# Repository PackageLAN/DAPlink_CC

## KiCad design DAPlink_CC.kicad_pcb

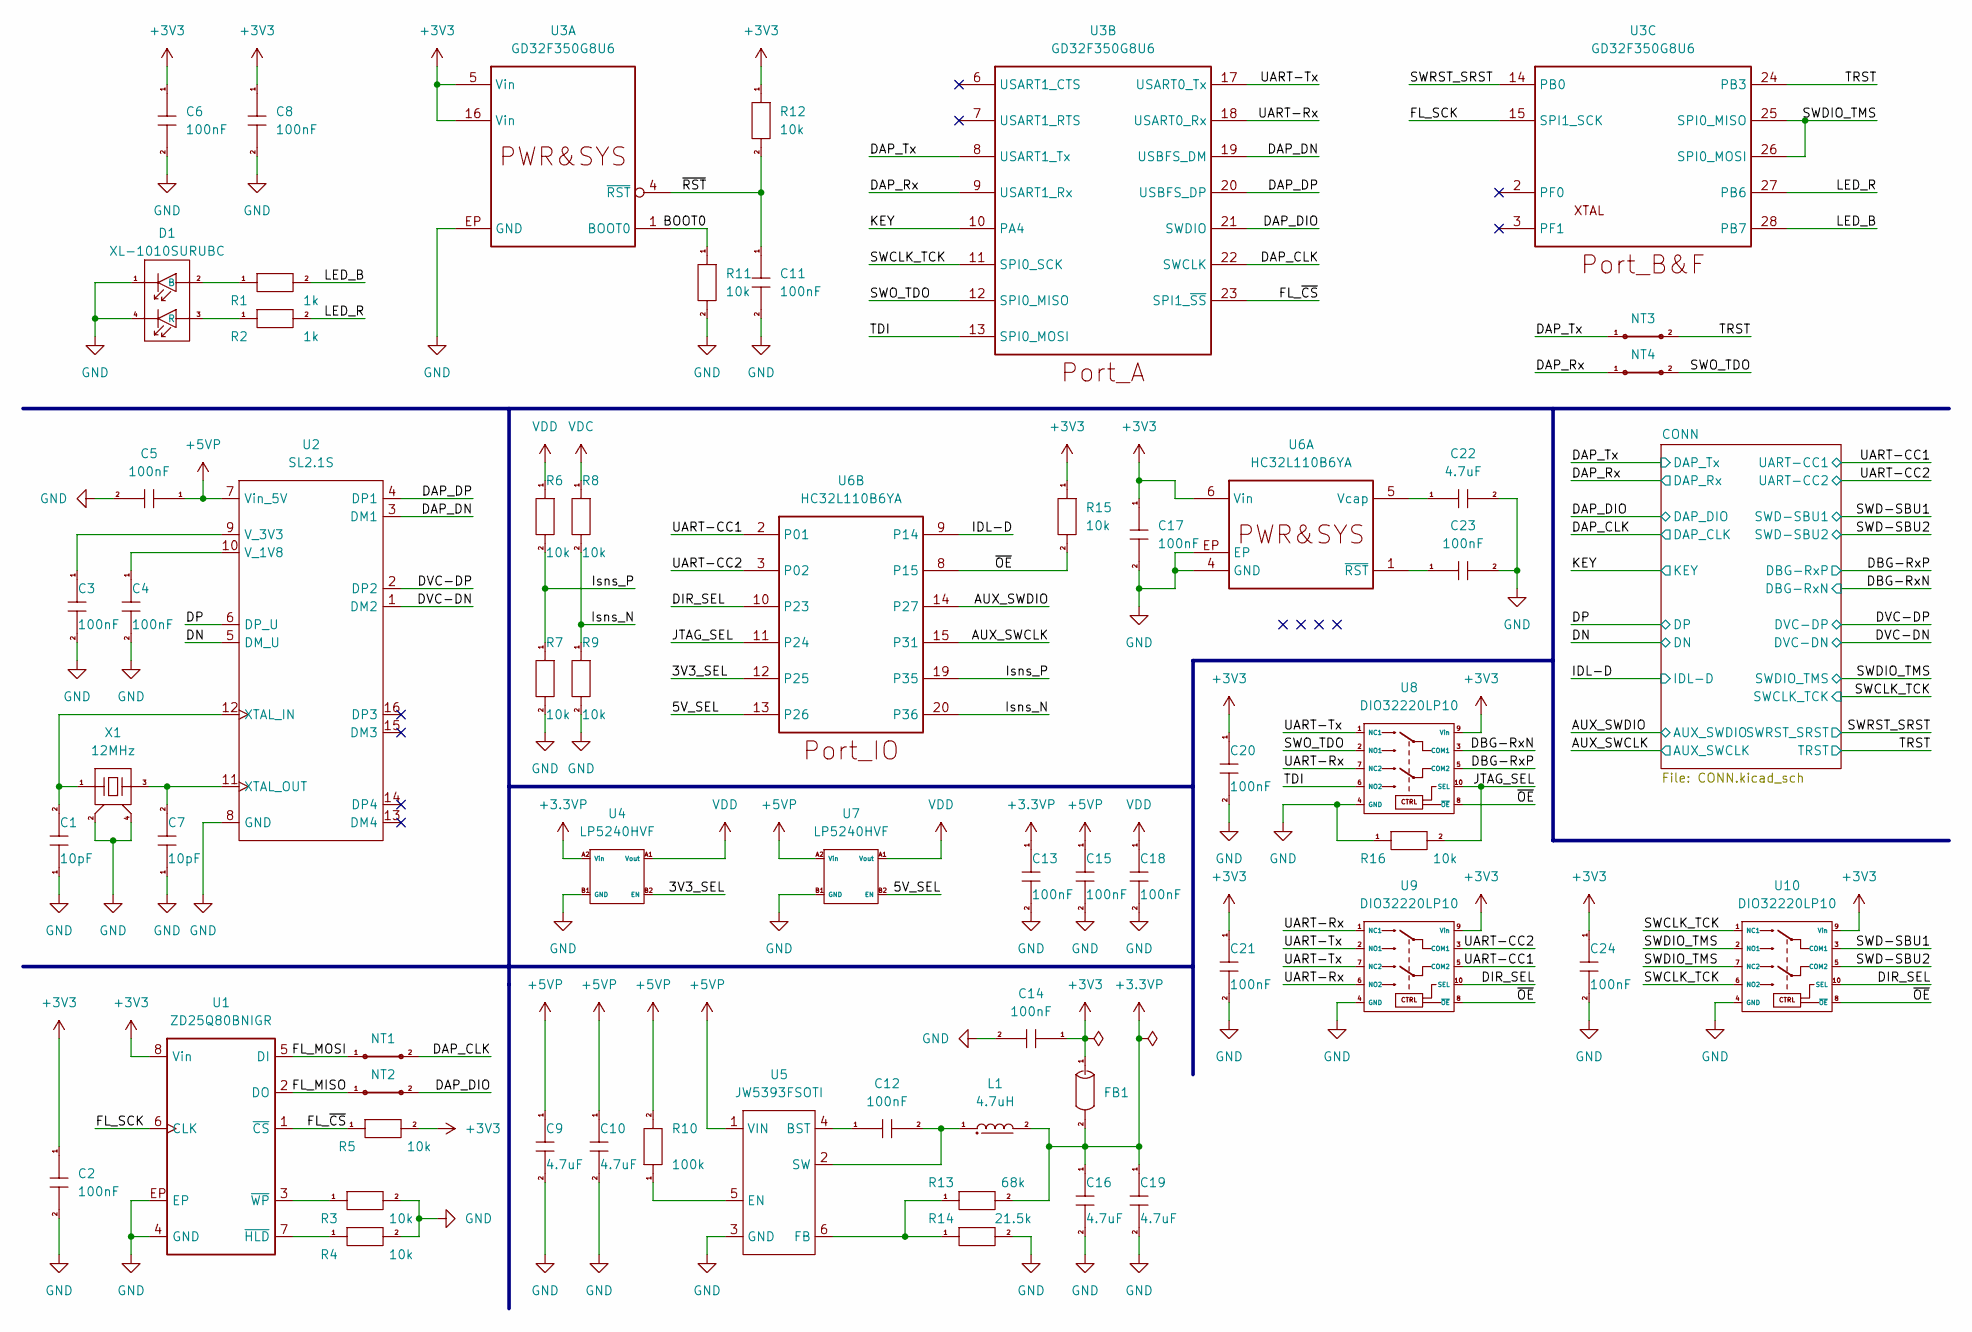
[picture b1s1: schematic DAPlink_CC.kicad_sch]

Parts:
C1, C7: 10pF; C0201(0603M)
C2, C3, C4, C5, C6, C8, C11, C12, C14, C17, C20, C21, C23, C24: 100nF; C0201(0603M)
C9, C10, C16, C19: 4.7uF; C0402(1005M)
C13, C15, C18: 100nF; C0402(1005M)
C22: 4.7uF; C0201(0603M)
D1: XL-1010SURUBC; LED-4_1010
FB1: 120R_100MHz; L0603(1608M)
L1: 4.7uH; MC-2520
NT1, NT2, NT3, NT4: NetCNVT-2; NetCNVT
R1, R2: 1k; R0201(0603M)
R3, R4, R5, R6, R7, R8, R9, R11, R12, R15, R16: 10k; R0201(0603M)
R10: 100k; R0201(0603M)
R13: 68k; R0201(0603M)
R14: 21.5k; R0201(0603M)
U1: ZD25Q80BNIGR; DFN-8_1515
U2: SL2.1S; MSOP-16_2646
U3: GD32F350G8U6; QFN-28_4040
U4, U7: LP5240HVF; CSP-4_S7575
U5: JW5393FSOTI; SOT-563
U6: HC32L110B6YA; QFN-20_3030
U8, U9, U10: DIO32220LP10; QFN-10_1814
X1: 12MHz; CXO-4_2520

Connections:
+3.3VP: C13.1, C16.1, C19.1, FB1.2, L1.2, R13.2, U4.A2 (Vin)
+3V3: C2.1, C6.1, C8.1, C14.1, C17.1, C20.1, C21.1, C24.1, FB1.1, R5.2, R12.1, R15.1, U1.8 (Vin), U3.5 (Vin), U3.16 (Vin), U6.6 (Vin), U8.9 (Vin), U9.9 (Vin), U10.9 (Vin); also elsewhere on the board
+5VP: C5.1, C9.1, C10.1, C15.1, R10.2, U2.7 (Vin_5V), U5.1 (VIN), U7.A2 (Vin); also elsewhere on the board
/3V3_SEL: U4.B2 (EN), U6.12 (P25)
/5V_SEL: U6.13 (P26), U7.B2 (EN)
/AUX_SWCLK: U6.15 (P31); also elsewhere on the board
/AUX_SWDIO: U6.14 (P27); also elsewhere on the board
/BOOT0: R11.1, U3.1 (BOOT0)
/DAP_CLK: NT1.2, U3.22 (SWCLK); also elsewhere on the board
/DAP_DIO: NT2.2, U3.21 (SWDIO); also elsewhere on the board
/DAP_DN: U2.3 (DM1), U3.19 (USBFS_DM)
/DAP_DP: U2.4 (DP1), U3.20 (USBFS_DP)
/DAP_Rx: NT4.1, U3.9 (USART1_Rx); also elsewhere on the board
/DAP_Tx: NT3.1, U3.8 (USART1_Tx); also elsewhere on the board
/DBG-RxN: U8.3 (COM1); also elsewhere on the board
/DBG-RxP: U8.5 (COM2); also elsewhere on the board
/DIR_SEL: U6.10 (P23), U9.10 (SEL), U10.10 (SEL)
/DN: U2.5 (DM_U); also elsewhere on the board
/DP: U2.6 (DP_U); also elsewhere on the board
/DVC-DN: U2.1 (DM2); also elsewhere on the board
/DVC-DP: U2.2 (DP2); also elsewhere on the board
/FL_MISO: NT2.1, U1.2 (DO)
/FL_MOSI: NT1.1, U1.5 (DI)
/FL_SCK: U1.6 (CLK), U3.15 (SPI1_SCK)
/FL_~CS: R5.1, U1.1 (~CS), U3.23 (SPI1_~SS)
/IDL-D: U6.9 (P14); also elsewhere on the board
/Isns_N: R8.2, R9.1, U6.20 (P36)
/Isns_P: R6.2, R7.1, U6.19 (P35)
/JTAG_SEL: R16.2, U6.11 (P24), U8.10 (SEL)
/KEY: U3.10 (PA4); also elsewhere on the board
/LED_B: R1.2, U3.28 (PB7)
/LED_R: R2.2, U3.27 (PB6)
/SWCLK_TCK: U3.11 (SPI0_SCK), U10.1 (NC1), U10.6 (NO2); also elsewhere on the board
/SWD-SBU1: U10.3 (COM1); also elsewhere on the board
/SWD-SBU2: U10.5 (COM2); also elsewhere on the board
/SWDIO_TMS: U3.25 (SPI0_MISO), U3.26 (SPI0_MOSI), U10.2 (NO1), U10.7 (NC2); also elsewhere on the board
/SWO_TDO: NT4.2, U3.12 (SPI0_MISO), U8.2 (NO1)
/SWRST_SRST: U3.14 (PB0); also elsewhere on the board
/TDI: U3.13 (SPI0_MOSI), U8.6 (NO2)
/TRST: NT3.2, U3.24 (PB3); also elsewhere on the board
/UART-CC1: U6.2 (P01), U9.5 (COM2); also elsewhere on the board
/UART-CC2: U6.3 (P02), U9.3 (COM1); also elsewhere on the board
/UART-Rx: U3.18 (USART0_Rx), U8.7 (NC2), U9.1 (NC1), U9.6 (NO2)
/UART-Tx: U3.17 (USART0_Tx), U8.1 (NC1), U9.2 (NO1), U9.7 (NC2)
/~OE: R15.2, U6.8 (P15), U8.8 (~OE), U9.8 (~OE), U10.8 (~OE)
/~RST: C11.1, R12.2, U3.4 (~RST)
GND: C1.1, C2.2, C3.2, C4.2, C5.2, C6.2, C7.1, C8.2, C9.2, C10.2, C11.2, C13.2, C14.2, C15.2, C16.2, C17.2, C18.2, C19.2, C20.2, C21.2, C22.2, C23.2, C24.2, D1.1 (Cathode), D1.4 (Cathode), R3.2, R4.2, R7.2, R9.2, R11.2, R14.2, R16.1, U1.4 (GND), U1.EP, U2.8 (GND), U3.EP (GND), U4.B1 (GND), U5.3 (GND), U6.4 (GND), U6.EP, U7.B1 (GND), U8.4 (GND), U9.4 (GND), U10.4 (GND), X1.2, X1.4; also elsewhere on the board
unnamed: C1.2, U2.12 (XTAL_IN), X1.1
unnamed: C3.1, U2.9 (V_3V3)
unnamed: C4.1, U2.10 (V_1V8)
unnamed: C7.2, U2.11 (XTAL_OUT), X1.3
unnamed: C12.1, U5.4 (BST)
unnamed: C12.2, L1.1, U5.2 (SW)
unnamed: C22.1, U6.5 (Vcap)
unnamed: C23.1, U6.1 (~RST)
unnamed: D1.2 (Anode), R1.1
unnamed: D1.3 (Anode), R2.1
unnamed: R3.1, U1.3 (~WP)
unnamed: R4.1, U1.7 (~HLD)
unnamed: R10.1, U5.5 (EN)
unnamed: R13.1, R14.1, U5.6 (FB)
VDC: R8.1; also elsewhere on the board
VDD: C18.1, R6.1, U4.A1 (Vout), U7.A1 (Vout); also elsewhere on the board

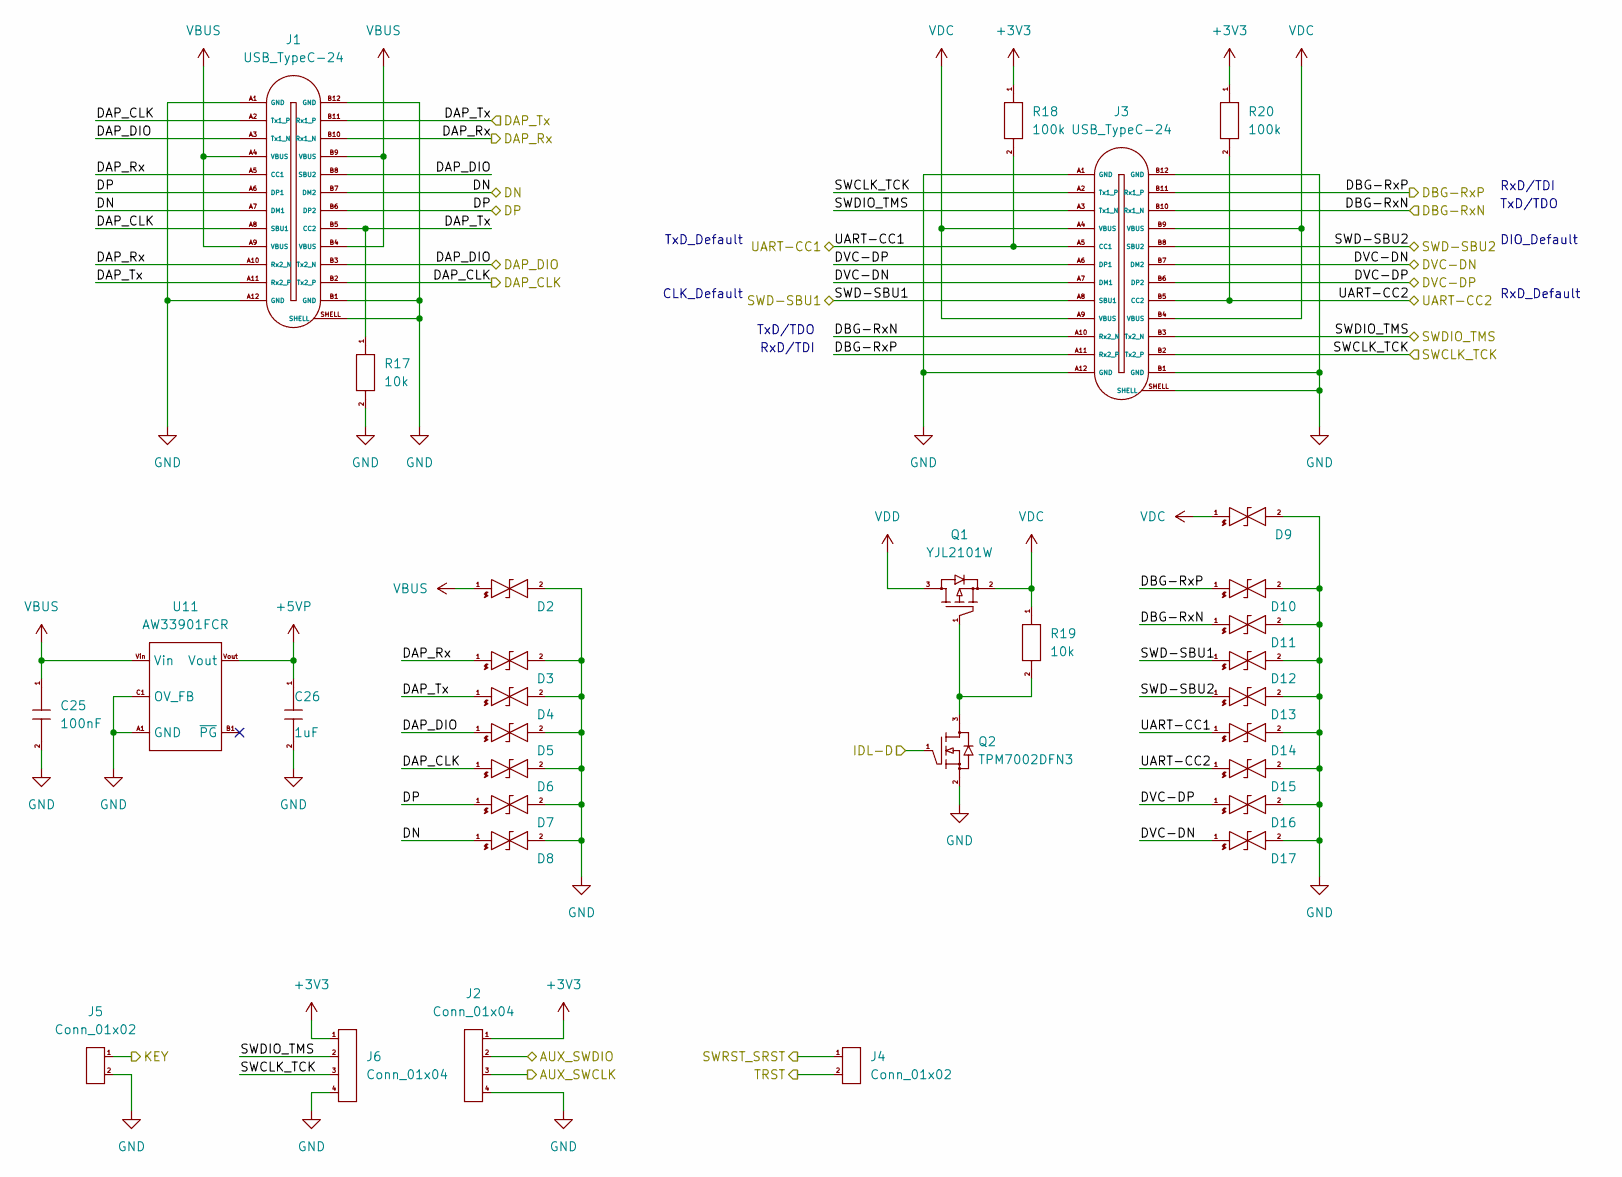
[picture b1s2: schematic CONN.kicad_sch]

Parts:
C25: 100nF; C0201(0603M)
C26: 1uF; C0402(1005M)
D2, D3, D4, D5, D6, D7, D8, D9, D10, D11, D12, D13, D14, D15, D16, D17: LESD11LL5.0CT5G; DFN-2_0603
J1: USB_TypeC-24; SCF-24_7925SST
J2, J6: Conn_01x04; VM-01x04_1mm
J3: USB_TypeC-24; SCM-24_L1402SST
J4, J5: Conn_01x02; VM-01x02_1mm
Q1: YJL2101W; SOT-323
Q2: TPM7002DFN3; DFN-3_1006
R17, R19: 10k; R0201(0603M)
R18, R20: 100k; R0402(1005M)
U11: AW33901FCR; LGA-9_1212_LSW

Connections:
+3V3: J2.1, J6.1, R18.1, R20.1; also elsewhere on the board
+5VP: C26.1, U11.Vout; also elsewhere on the board
/AUX_SWCLK: J2.3; also elsewhere on the board
/AUX_SWDIO: J2.2; also elsewhere on the board
/DAP_CLK: D6.1 (Cathode), J1.A2 (Tx1_P), J1.A8 (SBU1), J1.B2 (Tx2_P); also elsewhere on the board
/DAP_DIO: D5.1 (Cathode), J1.A3 (Tx1_N), J1.B3 (Tx2_N), J1.B8 (SBU2); also elsewhere on the board
/DAP_Rx: D3.1 (Cathode), J1.A5 (CC1), J1.A10 (Rx2_N), J1.B10 (Rx1_N); also elsewhere on the board
/DAP_Tx: D4.1 (Cathode), J1.A11 (Rx2_P), J1.B5 (CC2), J1.B11 (Rx1_P), R17.1; also elsewhere on the board
/DBG-RxN: D11.1 (Cathode), J3.A10 (Rx2_N), J3.B10 (Rx1_N); also elsewhere on the board
/DBG-RxP: D10.1 (Cathode), J3.A11 (Rx2_P), J3.B11 (Rx1_P); also elsewhere on the board
/DN: D8.1 (Cathode), J1.A7 (DM1), J1.B7 (DM2); also elsewhere on the board
/DP: D7.1 (Cathode), J1.A6 (DP1), J1.B6 (DP2); also elsewhere on the board
/DVC-DN: D17.1 (Cathode), J3.A7 (DM1), J3.B7 (DM2); also elsewhere on the board
/DVC-DP: D16.1 (Cathode), J3.A6 (DP1), J3.B6 (DP2); also elsewhere on the board
/IDL-D: Q2.1 (Gate); also elsewhere on the board
/KEY: J5.1; also elsewhere on the board
/SWCLK_TCK: J3.A2 (Tx1_P), J3.B2 (Tx2_P), J6.3; also elsewhere on the board
/SWD-SBU1: D12.1 (Cathode), J3.A8 (SBU1); also elsewhere on the board
/SWD-SBU2: D13.1 (Cathode), J3.B8 (SBU2); also elsewhere on the board
/SWDIO_TMS: J3.A3 (Tx1_N), J3.B3 (Tx2_N), J6.2; also elsewhere on the board
/SWRST_SRST: J4.1; also elsewhere on the board
/TRST: J4.2; also elsewhere on the board
/UART-CC1: D14.1 (Cathode), J3.A5 (CC1), R18.2; also elsewhere on the board
/UART-CC2: D15.1 (Cathode), J3.B5 (CC2), R20.2; also elsewhere on the board
GND: C25.2, C26.2, D2.2 (Anode), D3.2 (Anode), D4.2 (Anode), D5.2 (Anode), D6.2 (Anode), D7.2 (Anode), D8.2 (Anode), D9.2 (Anode), D10.2 (Anode), D11.2 (Anode), D12.2 (Anode), D13.2 (Anode), D14.2 (Anode), D15.2 (Anode), D16.2 (Anode), D17.2 (Anode), J1.A1 (GND), J1.A12 (GND), J1.B1 (GND), J1.B12 (GND), J1.SHELL, J2.4, J3.A1 (GND), J3.A12 (GND), J3.B1 (GND), J3.B12 (GND), J3.SHELL, J5.2, J6.4, Q2.2 (Source), R17.2, U11.A1 (GND), U11.C1 (OV_FB); also elsewhere on the board
unnamed: Q1.1 (Gate), Q2.3 (Drain), R19.2
VBUS: C25.1, D2.1 (Cathode), J1.A4 (VBUS), J1.A9 (VBUS), J1.B4 (VBUS), J1.B9 (VBUS), U11.Vin
VDC: D9.1 (Cathode), J3.A4 (VBUS), J3.A9 (VBUS), J3.B4 (VBUS), J3.B9 (VBUS), Q1.2 (Source), R19.1; also elsewhere on the board
VDD: Q1.3 (Drain); also elsewhere on the board

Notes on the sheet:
RxD/TDI
TxD_Default
CLK_Default
RxD_Default
TxD/TDO
DIO_Default

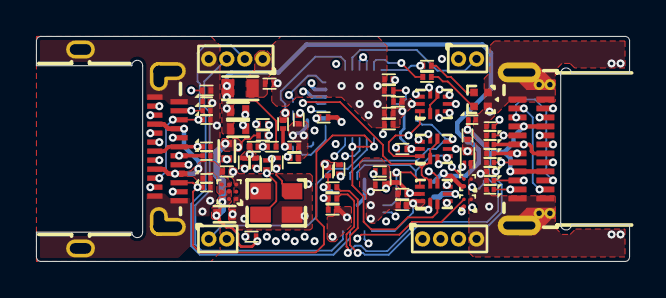
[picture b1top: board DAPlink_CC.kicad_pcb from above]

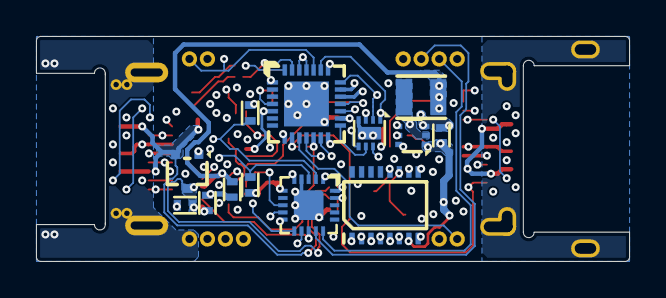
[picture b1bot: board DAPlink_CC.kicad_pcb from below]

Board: 6 copper layers, 33.0 x 12.5 mm, 89 parts (16 on the bottom side), 65 nets.

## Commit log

2022-12-06 Create project
2022-12-12 Update schematics
2022-12-12 Complete schematics
    Nightly update
2022-12-13 Nightly update
2022-12-14 Complete package assignments
2022-12-14 Update layout
2022-12-14 Update layout
    Nightly update
2022-12-17 Daily update
2023-01-11 Correction line order of SCF CONN
